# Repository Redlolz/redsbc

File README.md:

# RedSBC

A dev board based on [this design](http://z80.info/gfx/z80test.gif) from [z80.info](http://z80.info/).

It's not done or tested yet.

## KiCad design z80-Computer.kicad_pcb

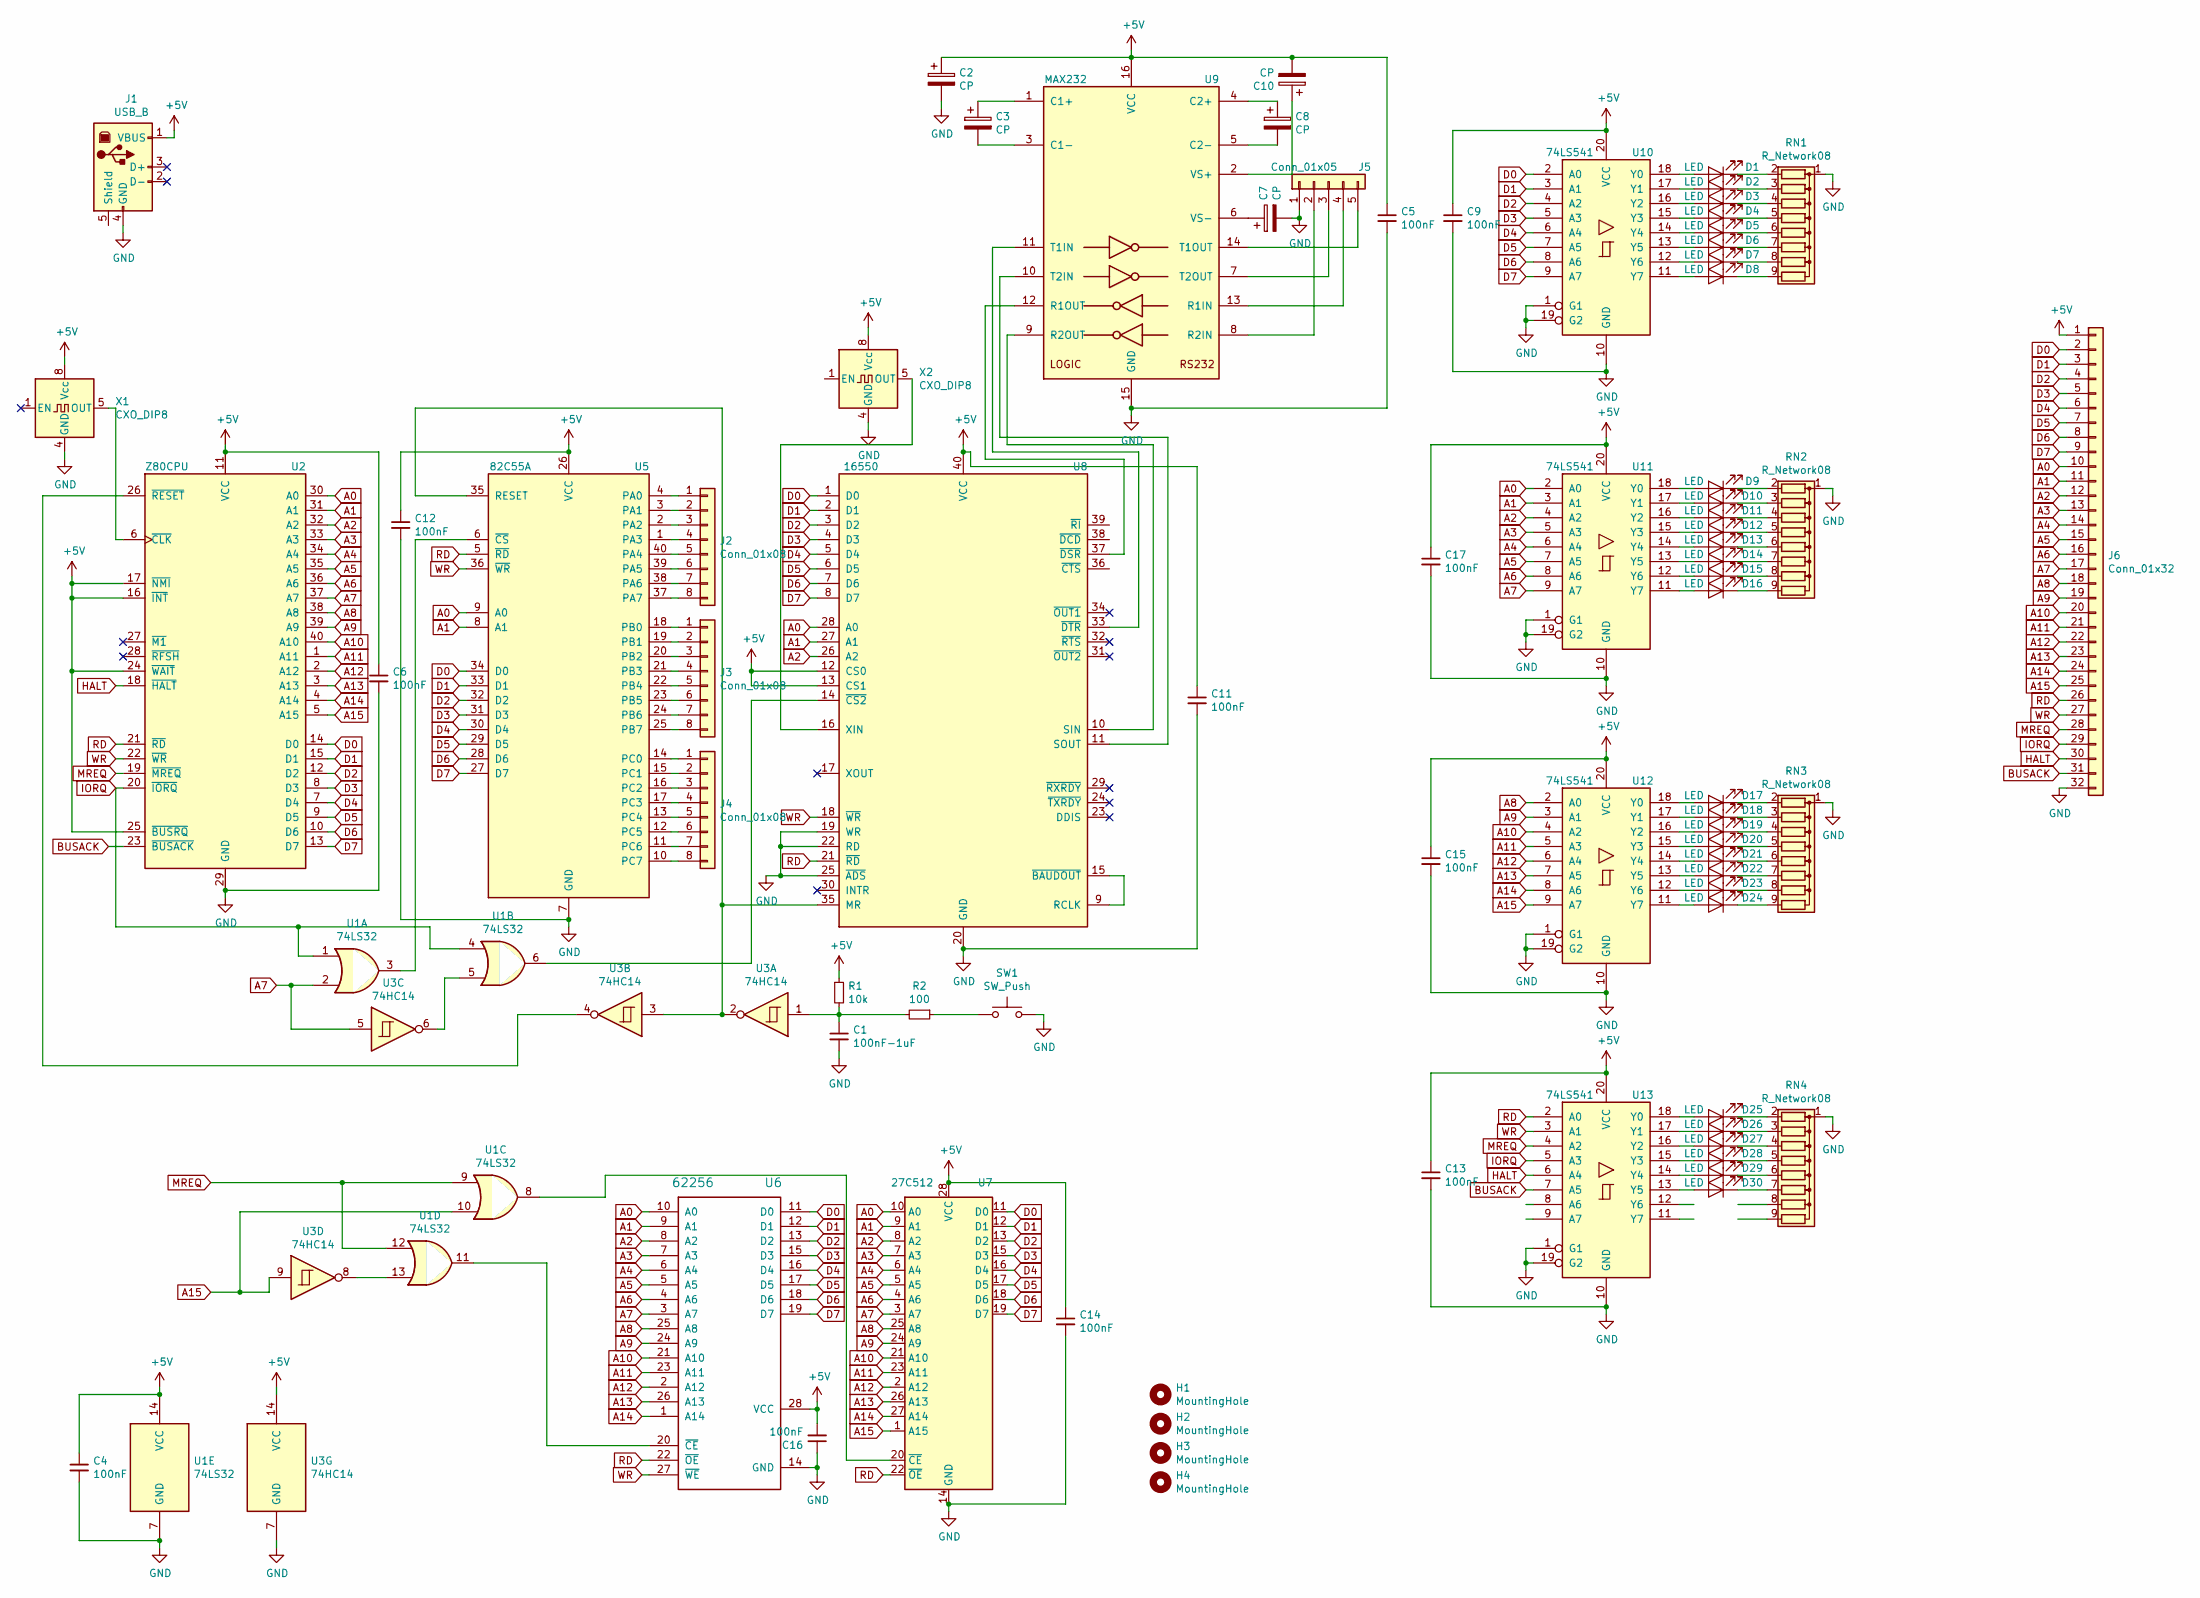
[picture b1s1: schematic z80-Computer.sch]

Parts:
C1: 100nF-1uF; C_Disc_D8.0mm_W2.5mm_P5.00mm
C2, C3, C7, C8, C10: CP; CP_Radial_D4.0mm_P1.50mm
C4, C5, C6, C9, C11, C12, C13, C14, C15, C16, C17: 100nF; C_Disc_D8.0mm_W2.5mm_P5.00mm
D1, D2, D3, D4, D5, D6, D7, D8, D9, D10, D11, D12, D13, D14, D15, D16, D17, D18, D19, D20, D21, D22, D23, D24, D25, D26, D27, D28, D29, D30: LED; LED_D5.0mm
H1, H2, H3, H4: MountingHole; MountingHole_2.2mm_M2
J1: USB_B; USB_B_OST_USB-B1HSxx_Horizontal
J2, J3, J4: Conn_01x08; PinHeader_1x08_P2.54mm_Vertical
J5: Conn_01x05; PinHeader_1x05_P2.54mm_Vertical
J6: Conn_01x32; PinHeader_1x32_P2.54mm_Vertical
R1: 10k; R_Axial_DIN0207_L6.3mm_D2.5mm_P10.16mm_Horizontal
R2: 100; R_Axial_DIN0207_L6.3mm_D2.5mm_P10.16mm_Horizontal
RN1, RN2, RN3, RN4: R_Network08; R_Array_SIP9
SW1: SW_Push; SW_PUSH_6mm
U1: 74LS32; DIP-14_W7.62mm_LongPads
U2: Z80CPU; DIP-40_W15.24mm_LongPads
U3: 74HC14; DIP-14_W7.62mm_LongPads
U5: 82C55A; DIP-40_W15.24mm_LongPads
U6: 62256; DIP-28_W15.24mm_LongPads
U7: 27C512; DIP-28_W15.24mm_LongPads
U8: 16550; DIP-40_W15.24mm_LongPads
U9: MAX232; DIP-16_W7.62mm_LongPads
U10, U11, U12, U13: 74LS541; DIP-20_W7.62mm_LongPads
X1, X2: CXO_DIP8; Oscillator_DIP-8

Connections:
+5V: C2.1, C4.1, C5.1, C6.1, C9.1, C10.2, C11.1, C12.1, C13.1, C14.1, C15.1, C16.2, C17.1, J1.1 (VBUS), J6.1, R1.1, U1.14 (VCC), U2.11 (VCC), U2.16 (~INT~), U2.17 (~NMI~), U2.24 (~WAIT~), U2.25 (~BUSRQ~), U3.14 (VCC), U5.26 (VCC), U6.28 (VCC), U7.28 (VCC), U8.12 (CS0), U8.13 (CS1), U8.40 (VCC), U9.16 (VCC), U10.20 (VCC), U11.20 (VCC), U12.20 (VCC), U13.20 (VCC), X1.8 (Vcc), X2.8 (Vcc)
A0: J6.10, U2.30 (A0), U5.9 (A0), U6.10 (A0), U7.10 (A0), U8.28 (A0), U11.2 (A0)
A1: J6.11, U2.31 (A1), U5.8 (A1), U6.9 (A1), U7.9 (A1), U8.27 (A1), U11.3 (A1)
A2: J6.12, U2.32 (A2), U6.8 (A2), U7.8 (A2), U8.26 (A2), U11.4 (A2)
A3: J6.13, U2.33 (A3), U6.7 (A3), U7.7 (A3), U11.5 (A3)
A4: J6.14, U2.34 (A4), U6.6 (A4), U7.6 (A4), U11.6 (A4)
A5: J6.15, U2.35 (A5), U6.5 (A5), U7.5 (A5), U11.7 (A5)
A6: J6.16, U2.36 (A6), U6.4 (A6), U7.4 (A6), U11.8 (A6)
A7: J6.17, U1.2, U2.37 (A7), U3.5, U6.3 (A7), U7.3 (A7), U11.9 (A7)
A8: J6.18, U2.38 (A8), U6.25 (A8), U7.25 (A8), U12.2 (A0)
A9: J6.19, U2.39 (A9), U6.24 (A9), U7.24 (A9), U12.3 (A1)
A10: J6.20, U2.40 (A10), U6.21 (A10), U7.21 (A10), U12.4 (A2)
A11: J6.21, U2.1 (A11), U6.23 (A11), U7.23 (A11), U12.5 (A3)
A12: J6.22, U2.2 (A12), U6.2 (A12), U7.2 (A12), U12.6 (A4)
A13: J6.23, U2.3 (A13), U6.26 (A13), U7.26 (A13), U12.7 (A5)
A14: J6.24, U2.4 (A14), U6.1 (A14), U7.27 (A14), U12.8 (A6)
A15: J6.25, U1.10, U2.5 (A15), U3.9, U7.1 (A15), U12.9 (A7)
BUSACK: J6.31, U2.23 (~BUSACK~), U13.7 (A5)
D0: J6.2, U2.14 (D0), U5.34 (D0), U6.11 (D0), U7.11 (D0), U8.1 (D0), U10.2 (A0)
D1: J6.3, U2.15 (D1), U5.33 (D1), U6.12 (D1), U7.12 (D1), U8.2 (D1), U10.3 (A1)
D2: J6.4, U2.12 (D2), U5.32 (D2), U6.13 (D2), U7.13 (D2), U8.3 (D2), U10.4 (A2)
D3: J6.5, U2.8 (D3), U5.31 (D3), U6.15 (D3), U7.15 (D3), U8.4 (D3), U10.5 (A3)
D4: J6.6, U2.7 (D4), U5.30 (D4), U6.16 (D4), U7.16 (D4), U8.5 (D4), U10.6 (A4)
D5: J6.7, U2.9 (D5), U5.29 (D5), U6.17 (D5), U7.17 (D5), U8.6 (D5), U10.7 (A5)
D6: J6.8, U2.10 (D6), U5.28 (D6), U6.18 (D6), U7.18 (D6), U8.7 (D6), U10.8 (A6)
D7: J6.9, U2.13 (D7), U5.27 (D7), U6.19 (D7), U7.19 (D7), U8.8 (D7), U10.9 (A7)
GND: C1.2, C2.2, C4.2, C5.2, C6.2, C7.2, C9.2, C11.2, C12.2, C13.2, C14.2, C15.2, C16.1, C17.2, J1.4 (GND), J5.1, J6.32, RN1.1 (common), RN2.1 (common), RN3.1 (common), RN4.1 (common), SW1.2, U1.7 (GND), U2.29 (GND), U3.7 (GND), U5.7 (GND), U6.14 (GND), U7.14 (GND), U8.19 (WR), U8.20 (GND), U8.22 (RD), U8.25 (~ADS~), U9.15 (GND), U10.1 (G1), U10.10 (GND), U10.19 (G2), U11.1 (G1), U11.10 (GND), U11.19 (G2), U12.1 (G1), U12.10 (GND), U12.19 (G2), U13.1 (G1), U13.10 (GND), U13.19 (G2), X1.4 (GND), X2.4 (GND)
HALT: J6.30, U2.18 (~HALT~), U13.6 (A4)
IORQ: J6.29, U1.1, U1.4, U2.20 (~IORQ~), U13.5 (A3)
MREQ: J6.28, U1.9, U1.12, U2.19 (~MREQ~), U13.4 (A2)
unnamed: C1.1, R1.2, R2.2, U3.1
unnamed: C3.1, U9.1 (C1+)
unnamed: C3.2, U9.3 (C1-)
unnamed: C7.1, U9.6 (VS-)
unnamed: C8.1, U9.4 (C2+)
unnamed: C8.2, U9.5 (C2-)
unnamed: C10.1, U9.2 (VS+)
unnamed: D1.1 (K), RN1.2 (R1)
unnamed: D1.2 (A), U10.18 (Y0)
unnamed: D2.1 (K), RN1.3 (R2)
unnamed: D2.2 (A), U10.17 (Y1)
unnamed: D3.1 (K), RN1.4 (R3)
unnamed: D3.2 (A), U10.16 (Y2)
unnamed: D4.1 (K), RN1.5 (R4)
unnamed: D4.2 (A), U10.15 (Y3)
unnamed: D5.1 (K), RN1.6 (R5)
unnamed: D5.2 (A), U10.14 (Y4)
unnamed: D6.1 (K), RN1.7 (R6)
unnamed: D6.2 (A), U10.13 (Y5)
unnamed: D7.1 (K), RN1.8 (R7)
unnamed: D7.2 (A), U10.12 (Y6)
unnamed: D8.1 (K), RN1.9 (R8)
unnamed: D8.2 (A), U10.11 (Y7)
unnamed: D9.1 (K), RN2.2 (R1)
unnamed: D9.2 (A), U11.18 (Y0)
unnamed: D10.1 (K), RN2.3 (R2)
unnamed: D10.2 (A), U11.17 (Y1)
unnamed: D11.1 (K), RN2.4 (R3)
unnamed: D11.2 (A), U11.16 (Y2)
unnamed: D12.1 (K), RN2.5 (R4)
unnamed: D12.2 (A), U11.15 (Y3)
unnamed: D13.1 (K), RN2.6 (R5)
unnamed: D13.2 (A), U11.14 (Y4)
unnamed: D14.1 (K), RN2.7 (R6)
unnamed: D14.2 (A), U11.13 (Y5)
unnamed: D15.1 (K), RN2.8 (R7)
unnamed: D15.2 (A), U11.12 (Y6)
unnamed: D16.1 (K), RN2.9 (R8)
unnamed: D16.2 (A), U11.11 (Y7)
unnamed: D17.1 (K), RN3.2 (R1)
unnamed: D17.2 (A), U12.18 (Y0)
unnamed: D18.1 (K), RN3.3 (R2)
unnamed: D18.2 (A), U12.17 (Y1)
unnamed: D19.1 (K), RN3.4 (R3)
unnamed: D19.2 (A), U12.16 (Y2)
unnamed: D20.1 (K), RN3.5 (R4)
unnamed: D20.2 (A), U12.15 (Y3)
unnamed: D21.1 (K), RN3.6 (R5)
unnamed: D21.2 (A), U12.14 (Y4)
unnamed: D22.1 (K), RN3.7 (R6)
unnamed: D22.2 (A), U12.13 (Y5)
unnamed: D23.1 (K), RN3.8 (R7)
unnamed: D23.2 (A), U12.12 (Y6)
unnamed: D24.1 (K), RN3.9 (R8)
unnamed: D24.2 (A), U12.11 (Y7)
unnamed: D25.1 (K), RN4.2 (R1)
unnamed: D25.2 (A), U13.18 (Y0)
unnamed: D26.1 (K), RN4.3 (R2)
unnamed: D26.2 (A), U13.17 (Y1)
unnamed: D27.1 (K), RN4.4 (R3)
unnamed: D27.2 (A), U13.16 (Y2)
unnamed: D28.1 (K), RN4.5 (R4)
unnamed: D28.2 (A), U13.15 (Y3)
unnamed: D29.1 (K), RN4.6 (R5)
unnamed: D29.2 (A), U13.14 (Y4)
unnamed: D30.1 (K), RN4.7 (R6)
unnamed: D30.2 (A), U13.13 (Y5)
unnamed: J2.1, U5.4 (PA0)
unnamed: J2.2, U5.3 (PA1)
unnamed: J2.3, U5.2 (PA2)
unnamed: J2.4, U5.1 (PA3)
unnamed: J2.5, U5.40 (PA4)
unnamed: J2.6, U5.39 (PA5)
unnamed: J2.7, U5.38 (PA6)
unnamed: J2.8, U5.37 (PA7)
unnamed: J3.1, U5.18 (PB0)
unnamed: J3.2, U5.19 (PB1)
unnamed: J3.3, U5.20 (PB2)
unnamed: J3.4, U5.21 (PB3)
unnamed: J3.5, U5.22 (PB4)
unnamed: J3.6, U5.23 (PB5)
unnamed: J3.7, U5.24 (PB6)
unnamed: J3.8, U5.25 (PB7)
unnamed: J4.1, U5.14 (PC0)
unnamed: J4.2, U5.15 (PC1)
unnamed: J4.3, U5.16 (PC2)
unnamed: J4.4, U5.17 (PC3)
unnamed: J4.5, U5.13 (PC4)
unnamed: J4.6, U5.12 (PC5)
unnamed: J4.7, U5.11 (PC6)
unnamed: J4.8, U5.10 (PC7)
unnamed: J5.2, U9.8 (R2IN)
unnamed: J5.3, U9.7 (T2OUT)
unnamed: J5.4, U9.13 (R1IN)
unnamed: J5.5, U9.14 (T1OUT)
unnamed: R2.1, SW1.1
unnamed: U1.3, U5.6 (~CS~)
unnamed: U1.5, U3.6
unnamed: U1.6, U8.14 (~CS2~)
unnamed: U1.8, U7.20 (~CE)
unnamed: U1.11, U6.20 (~CE~)
unnamed: U1.13, U3.8
unnamed: U2.6 (~CLK~), X1.5 (OUT)
unnamed: U2.26 (~RESET~), U3.4
unnamed: U3.2, U3.3, U5.35 (RESET), U8.35 (MR)
unnamed: U8.10 (SIN), U9.9 (R2OUT)
unnamed: U8.11 (SOUT), U9.10 (T2IN)
unnamed: U8.9 (RCLK), U8.15 (~BAUDOUT~)
unnamed: U8.16 (XIN), X2.5 (OUT)
unnamed: U8.33 (~DTR~), U9.11 (T1IN)
unnamed: U8.37 (~DSR~), U9.12 (R1OUT)
RD: J6.26, U2.21 (~RD~), U5.5 (~RD~), U6.22 (~OE~), U7.22 (~OE), U8.21 (~RD~), U13.2 (A0)
WR: J6.27, U2.22 (~WR~), U5.36 (~WR~), U6.27 (~WE~), U8.18 (~WR~), U13.3 (A1)

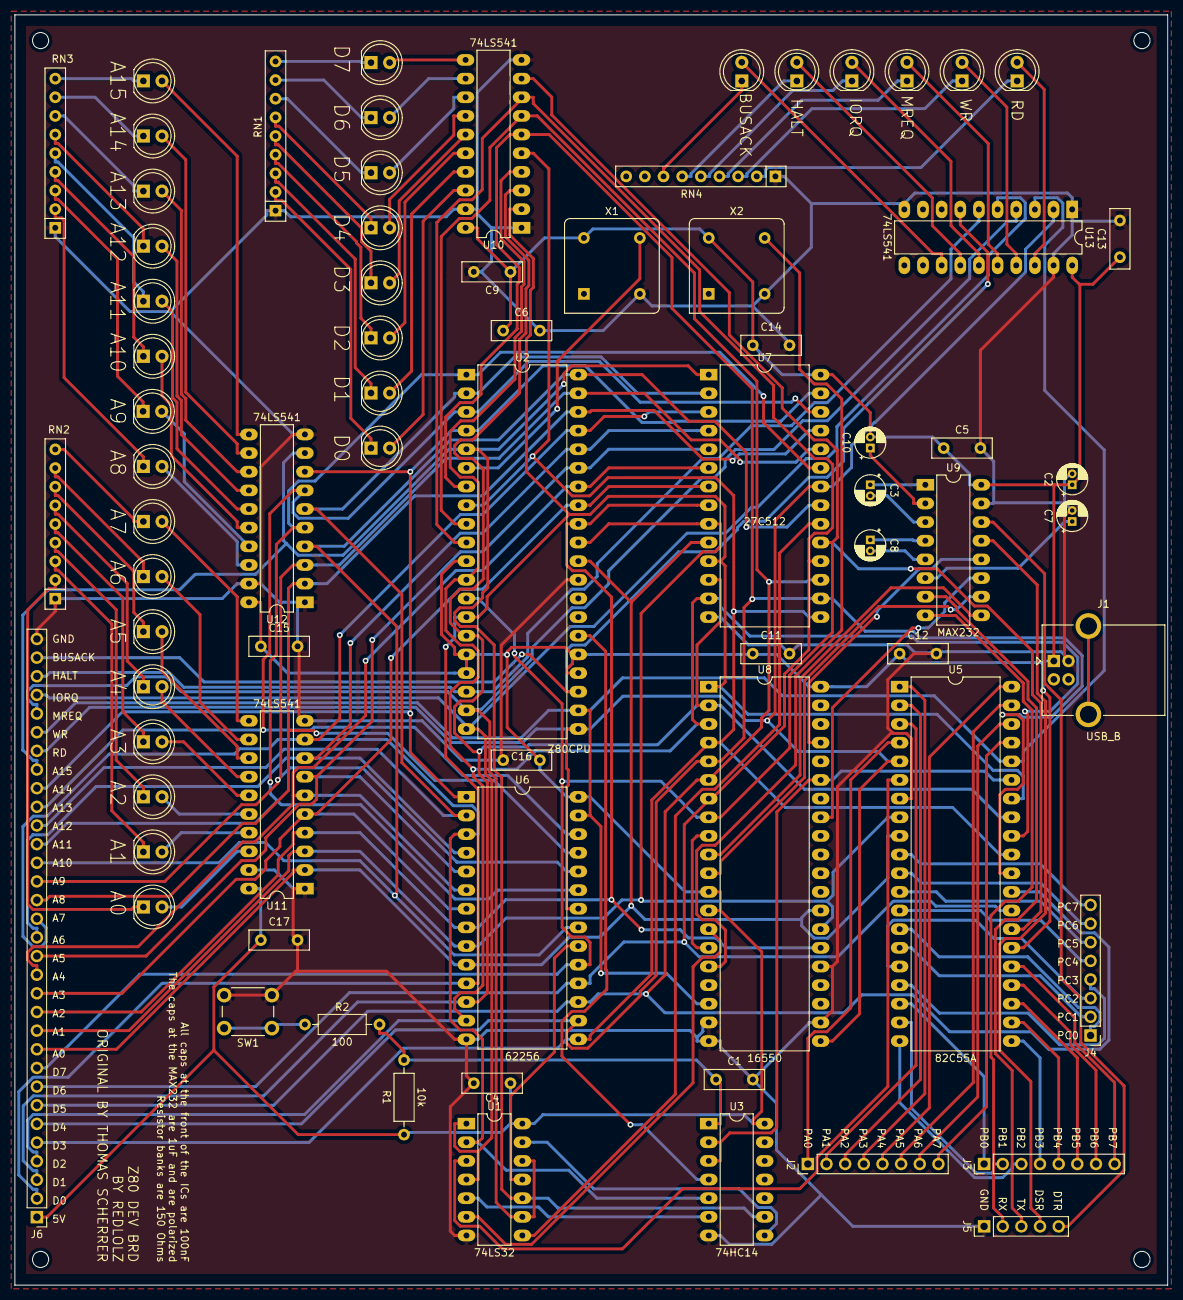
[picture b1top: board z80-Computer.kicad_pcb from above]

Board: 2 copper layers, 157.0 x 173.0 mm, 78 parts (0 on the bottom side), 143 nets.
